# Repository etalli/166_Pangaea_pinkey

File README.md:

# Pinkey Extension module for Pangaea 1.2
MIT License

Pineky replacement modulet for Pangaea RI 1.2. The left hand end row is 0.25u lower than the left hand end row.
This is the physical layout used on many keyboards.  The 0.5u lower version is also availavle.

Compatible with Cherry MX and Choc switches as well as standard parts.

# note

You can use the same top plate as the Same-special, which is not included here. It is included in Pangaea's standard package, so please use that.

# history

* 3/21 initial version
* 11/5 Added pictures

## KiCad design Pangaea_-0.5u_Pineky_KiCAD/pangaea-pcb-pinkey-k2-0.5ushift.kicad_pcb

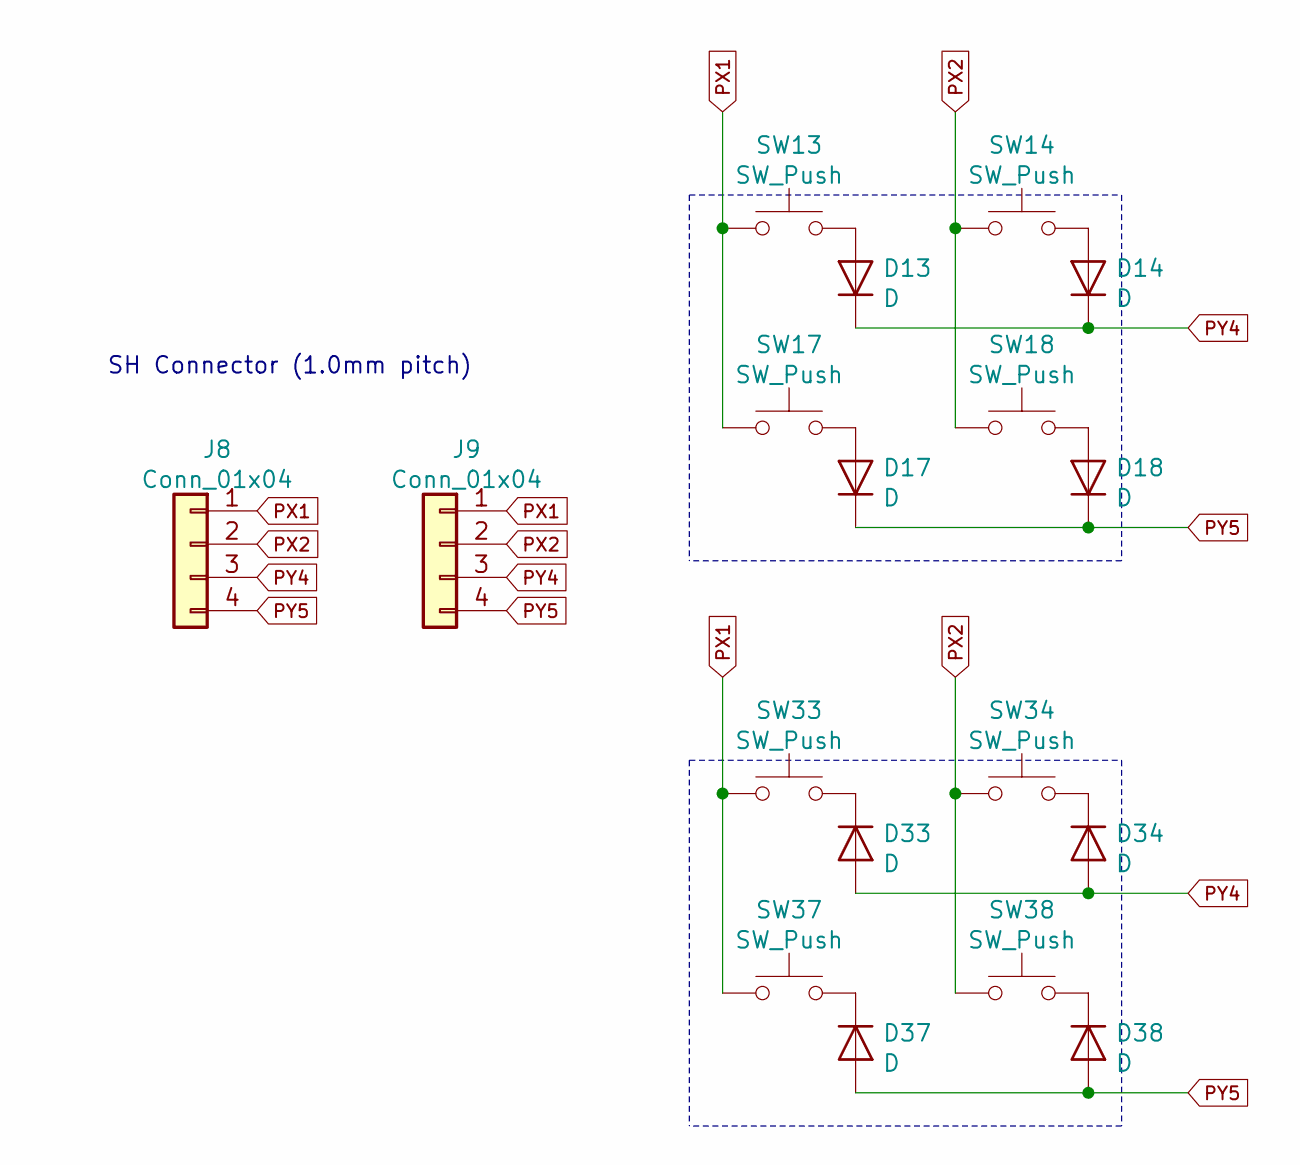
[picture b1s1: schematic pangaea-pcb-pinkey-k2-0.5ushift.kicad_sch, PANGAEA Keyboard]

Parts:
D13, D14, D17, D18, D33, D34, D37, D38: D; diode_TH_SMD_rev3
J8, J9: Conn_01x04; JST_SH_BM03B-SRSS-TB_1x04-1MP_P1.00mm_Vertical
SW13, SW14, SW17, SW18, SW33, SW34, SW37, SW38: SW_Push; CherryMX_Choc_Hotswap_rev9_test

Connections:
unnamed: D13.2 (A), SW13.2
unnamed: D14.2 (A), SW14.2
unnamed: D17.2 (A), SW17.2
unnamed: D18.2 (A), SW18.2
unnamed: D33.1 (K), SW33.2
unnamed: D34.1 (K), SW34.2
unnamed: D37.1 (K), SW37.2
unnamed: D38.1 (K), SW38.2
PX1: J8.1, J9.1, SW13.1, SW17.1, SW33.1, SW37.1
PX2: J8.2, J9.2, SW14.1, SW18.1, SW34.1, SW38.1
PY4: D13.1 (K), D14.1 (K), D33.2 (A), D34.2 (A), J8.3, J9.3
PY5: D17.1 (K), D18.1 (K), D37.2 (A), D38.2 (A), J8.4, J9.4

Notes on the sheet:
SH Connector (1.0mm pitch)

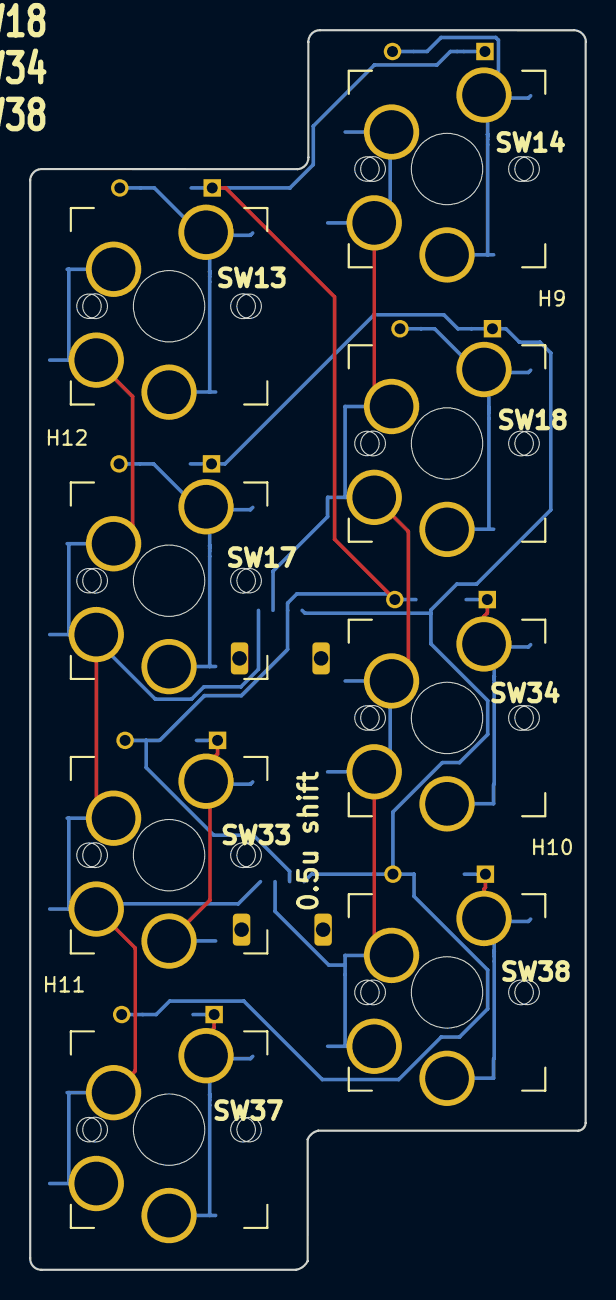
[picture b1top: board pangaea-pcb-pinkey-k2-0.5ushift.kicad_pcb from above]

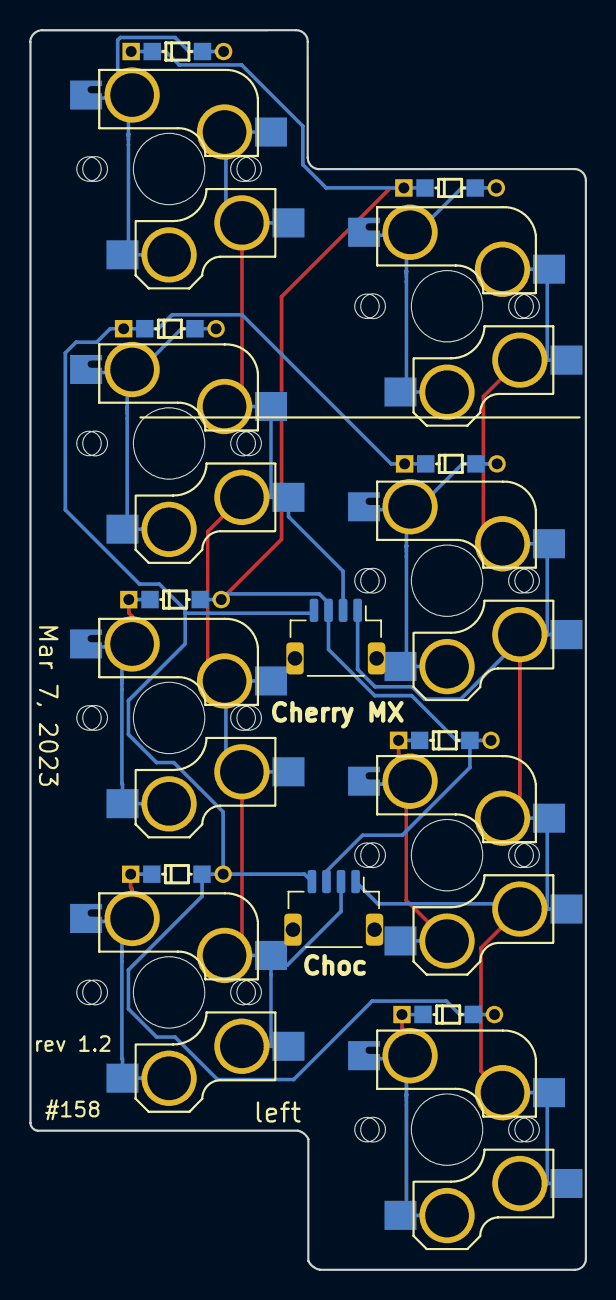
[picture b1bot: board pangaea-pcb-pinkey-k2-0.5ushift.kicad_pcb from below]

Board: 2 copper layers, 38.2 x 85.1 mm, 22 parts (2 on the bottom side), 12 nets.

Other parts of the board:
H9, H10, H11, H12: MountingHole; M2_Nut_Hole_rev2

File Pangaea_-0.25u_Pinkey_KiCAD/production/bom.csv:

Designator,Footprint,Quantity,Value,LCSC Part #
"D13, D14, D17, D18, D33, D34, D37, D38",diode_TH_SMD_rev3,8,D,
"H10, H11, H12, H9",M2_Nut_Hole_rev2,4,MountingHole,
"J8, J9",JST_SH_BM03B-SRSS-TB_1x04-1MP_P1.00mm_Vertical,2,Conn_01x04,
"SW13, SW14, SW17, SW18, SW33, SW34, SW37, SW38",CherryMX_Choc_Hotswap_rev9_test,8,SW_Push,

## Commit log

2023-10-15 merged 0.25u and 0.5u
2023-11-05 added pictures
2023-11-05 moved pictures to images dir.
